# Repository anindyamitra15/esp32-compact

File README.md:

# esp32-iot-socket
Most compact yet complete ESP32 based IoT Socket board

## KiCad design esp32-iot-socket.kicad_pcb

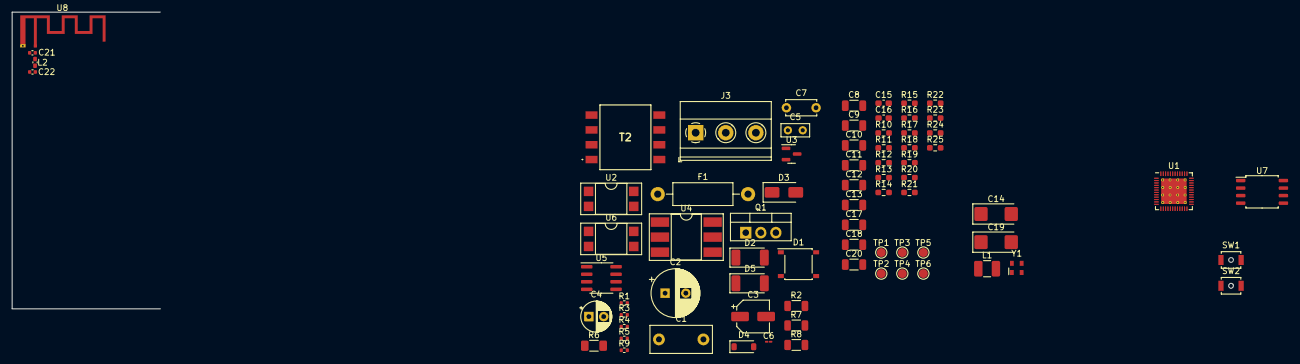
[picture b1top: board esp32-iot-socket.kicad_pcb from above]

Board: 4 copper layers, 75 parts (0 on the bottom side), 53 nets, no tracks yet.

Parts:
C1: 104J 400V; C_Rect_L10.3mm_W4.5mm_P7.50mm_MKS4
C2: 2.2uF 400V; CP_Radial_D8.0mm_P3.50mm
C3: 470uF 10V; CP_Elec_5x5.3
C4: 2.2uF 50V; CP_Radial_D5.0mm_P2.50mm
C5: 102; C_Rect_L4.6mm_W2.0mm_P2.50mm_MKS02_FKP02
C6: 47nF; C_01005_0402Metric_Pad0.57x0.30mm_HandSolder
C7: 102 2kV Y1; C_Disc_D5.0mm_W2.5mm_P5.00mm
C8, C9, C10, C11, C12, C13, C17, C18, C20: 100nF; C_1206_3216Metric
C14: 10uF; CP_EIA-6032-20_AVX-F_Pad2.25x2.35mm_HandSolder
C15, C16: 10pF; C_0603_1608Metric_Pad1.08x0.95mm_HandSolder
C19: 4.7uF; CP_EIA-6032-20_AVX-F_Pad2.25x2.35mm_HandSolder
C21, C22: 3.3pF; C_0402_1005Metric
D1: ABS10; Diode_Bridge_Diotec_ABS
D2, D5: SM4007; D_MELF
D3: B150-E3; D_SMA
D4: 1N4148W; D_SOD-123
F1: 0.5W 10; R_Axial_DIN0411_L9.9mm_D3.6mm_P15.24mm_Horizontal
J3: Screw_Terminal_01x03; TerminalBlock_Phoenix_MKDS-1,5-3-5.08_1x03_P5.08mm_Horizont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
L1: 2.2nH; L_1210_3225Metric_Pad1.42x2.65mm_HandSolder
L2: 2.2nH; L_0402_1005Metric_Pad0.77x0.64mm_HandSolder
Q1: BT136-800; TO-220-3_Vertical
R1, R9: 1.5k; R_0402_1005Metric
R2: 470; R_1206_3216Metric
R3, R5: 470; R_0402_1005Metric
R4: 4.7k; R_0402_1005Metric
R6: 82k; R_1206_3216Metric_Pad1.30x1.75mm_HandSolder
R7, R8: 150k; R_1206_3216Metric
R10, R13, R14, R17, R18, R19, R25: 22; R_0603_1608Metric_Pad0.98x0.95mm_HandSolder
R11, R12: 5.1k; R_0603_1608Metric_Pad0.98x0.95mm_HandSolder
R15, R16: 470; R_0603_1608Metric_Pad0.98x0.95mm_HandSolder
R20, R21, R22, R23, R24: 68k; R_0603_1608Metric_Pad0.98x0.95mm_HandSolder
SW1: Reset; SW_SPST_B3U-1000P-B
SW2: Boot; SW_SPST_B3U-1000P-B
T2: POE30P-33L; POE30P33L
TP1: 3.3V; TestPoint_Pad_D1.5mm
TP2: GND; TestPoint_Pad_D1.5mm
TP3: Rx; TestPoint_Pad_D1.5mm
TP4: Tx; TestPoint_Pad_D1.5mm
TP5: DTR; TestPoint_Pad_D1.5mm
TP6: RTS; TestPoint_Pad_D1.5mm
U1: ESP32-D0WDQ6; QFN-48-1EP_6x6mm_P0.4mm_EP4.3x4.3mm_ThermalVias
U2, U6: PC817; DIP-4_W7.62mm_SMDSocket_SmallPads
U3: TL431DBZ; SOT-23
U4: MOC3021M; DIP-6_W8.89mm_SMDSocket_LongPads
U5: VIPer22AS; SOIC-8_3.9x4.9mm_P1.27mm
U7: W25Q32JVSS; SOIC-8_5.23x5.23mm_P1.27mm
U8: ANTENNA 2.4GHz; Texas_SWRA117D_2.4GHz_Right
Y1: ABM10AIG; Oscillator_SMD_Abracon_ASDMB-4Pin_2.5x2.0mm

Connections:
+3V3: C3.1, C8.1, C9.1, C10.1, C11.1, C12.1, C14.1, D3.1 (K), L1.1, R1.2, R5.1, R9.1, R11.1, R12.1, R22.1, R23.1, TP1.1, U1.1 (VDDA), U1.19 (VDD3P3_RTC), U1.37 (VDD3P3_CPU), U1.43 (VDDA), U1.46 (VDDA)
/Microcontroller Section/3.3V RF: C13.1, L1.2, U1.3 (VDD3P3), U1.4 (VDD3P3)
/Microcontroller Section/Boot: C18.1, R12.2, R13.2, R18.1, U1.23 (GPIO0)
/Microcontroller Section/DTR: C17.1, R11.2, R14.1, R17.1, U1.9 (CHIP_PU)
/Microcontroller Section/Rx: R15.1, U1.40 (U0RXD)
/Microcontroller Section/SCK/CLK: U1.31 (SD_CLK), U7.6 (CLK)
/Microcontroller Section/SCS/CMD: U1.30 (SD_CMD), U7.1 (~CS)
/Microcontroller Section/SDI/SD1: U1.33 (SD_DATA_1), U7.5 (DI(IO0))
/Microcontroller Section/SDO/SD0: U1.32 (SD_DATA_0), U7.2 (DO(IO1))
/Microcontroller Section/SHD/SD2: U1.28 (SD_DATA_2), U7.7 (IO3)
/Microcontroller Section/SWP/SD3: U1.29 (SD_DATA_3), U7.3 (IO2)
/Microcontroller Section/TRIAC output: R3.2, R19.1
/Microcontroller Section/Tx: R16.1, U1.41 (U0TXD)
/Microcontroller Section/VDD_SDIO: C19.1, C20.1, R24.1, U1.26 (VDD_SDIO), U7.8 (VCC)
/Microcontroller Section/XTal_N: C16.1, U1.44 (XTAL_N), Y1.4
/Microcontroller Section/XTal_P: R10.1, U1.45 (XTAL_P)
/Microcontroller Section/ZVC signal in: R9.2, U1.16 (GPIO27), U6.4
/Power Supply Section/L: F1.1, J3.1, Q1.1 (A1)
GNDD: C3.2, C7.2, C8.2, C9.2, C10.2, C11.2, C12.2, C13.2, C14.2, C15.2, C16.2, C17.2, C18.2, C19.2, C20.2, C21.2, C22.2, R4.2, R20.1, R21.1, R24.2, SW1.1, SW2.1, T2.7 (SEC_3), T2.8 (SEC_4), TP2.1, U1.49 (GND), U3.3 (A), U4.2, U6.3, U7.4 (GND), U8.2 (Gnd), Y1.2, Y1.3
unnamed: C1.1, D1.4, F1.2
unnamed: C15.1, R10.2, Y1.1
unnamed: D1.1 (+), D5.2 (A), R8.2
unnamed: C2.2, C4.2, C6.2, C7.1, D1.2 (-), R7.1, T2.1 (BIAS_1), U5.1 (S), U5.2 (S)
unnamed: D2.2 (A), T2.3 (PRI_1), U5.5 (D), U5.6 (D), U5.7 (D), U5.8 (D)
unnamed: C5.2, D2.1 (K), R6.2
unnamed: D3.2 (A), T2.5 (SEC_1), T2.6 (SEC_2)
unnamed: D4.2 (A), T2.2 (BIAS_2)
unnamed: C4.1, D4.1 (K), U2.4, U5.4 (VDD)
unnamed: C2.1, C5.1, D5.1 (K), R6.1, T2.4 (PRI_2)
unnamed: C1.2, D1.3, J3.2
unnamed: J3.3, Q1.2 (A2), U4.6
unnamed: Q1.3 (G), R2.1
unnamed: R2.2, U4.4
unnamed: R3.1, U4.1
unnamed: R5.2, U2.1
unnamed: R7.2, U6.2
unnamed: R8.1, U6.1
unnamed: R13.1, SW2.2
unnamed: R14.2, SW1.2
unnamed: R15.2, TP3.1
unnamed: R16.2, TP4.1
unnamed: R17.2, TP5.1
unnamed: R18.2, TP6.1
unnamed: R20.2, U1.22 (GPIO2)
unnamed: R22.2, U1.34 (GPIO5)
unnamed: R19.2, U1.25 (GPIO16)
unnamed: C21.1, C22.1, L2.1, L2.2, U1.2 (LNA_IN), U8.1 (in)
unnamed: R25.2, U1.20 (MTCK)
unnamed: R21.2, U1.18 (MTDI)
unnamed: R23.2, U1.21 (MTDO)
unnamed: U2.2, U3.1 (K)
unnamed: R1.1, R4.1, U3.2 (REF)
unnamed: C6.1, U2.3, U5.3 (FB)

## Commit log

2023-07-30 init
2023-07-31 added ESP32 model
2023-07-31 proper esp32 footprint added
2023-08-01 hierarchical sheets
2023-08-05 progress in psu section:footprints added:flyback ic yet to be added
2023-08-06 viper22as, transformer, hierarchical connections
2023-08-06 completed psu schematic sheet
2023-08-07 added buttons, crystal, power caps
2023-08-08 added flash, uart
2023-08-09 added antenna symbol
2023-08-09 schematic completed:
